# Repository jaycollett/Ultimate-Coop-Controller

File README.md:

# Ultimate-Coop-Controller
Arduino controlled chicken coop sensing and automation

More details on this project soon....

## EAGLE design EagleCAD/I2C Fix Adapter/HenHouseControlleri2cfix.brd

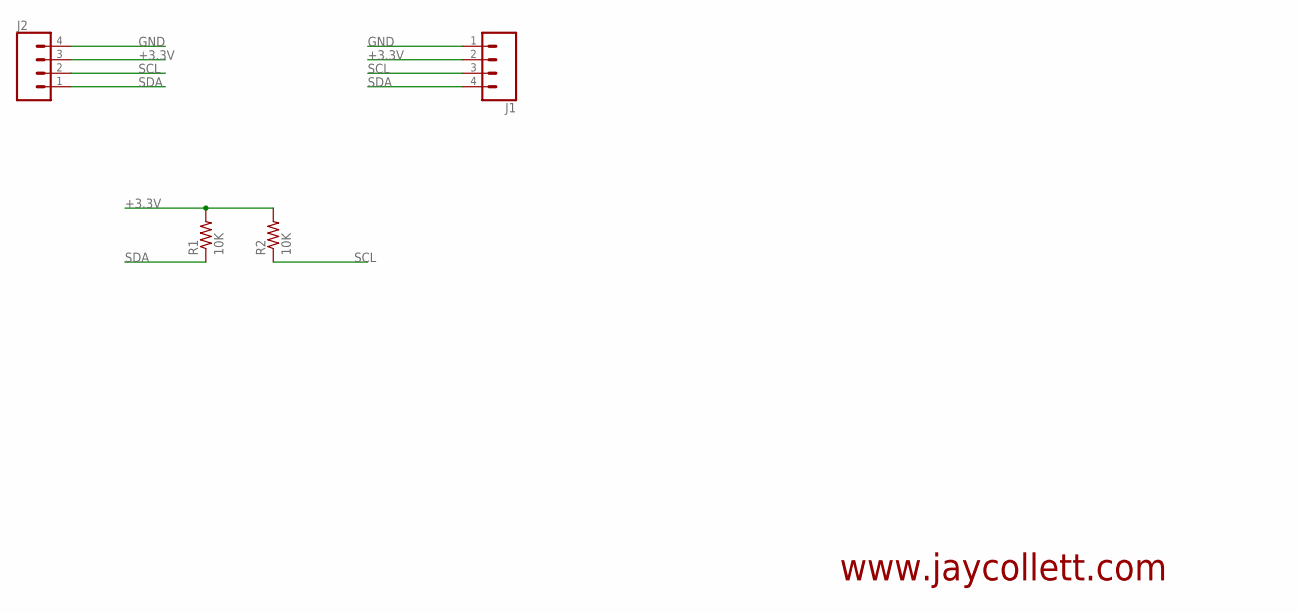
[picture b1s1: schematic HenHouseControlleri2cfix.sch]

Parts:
J1, J2: CONN_04LONGPADS; 1X04_LONGPADS
R1, R2: 10K; R0805

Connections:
+3.3V: J1.2, J2.3, R1.2, R2.2
GND: J1.1, J2.4
SCL: J1.3, J2.2, R2.1
SDA: J1.4, J2.1, R1.1

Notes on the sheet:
www.jaycollett.com

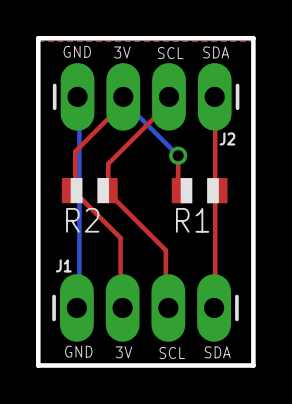
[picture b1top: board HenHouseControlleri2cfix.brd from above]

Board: 2 copper layers, 11.9 x 18.2 mm, 4 parts (0 on the bottom side), 4 nets.

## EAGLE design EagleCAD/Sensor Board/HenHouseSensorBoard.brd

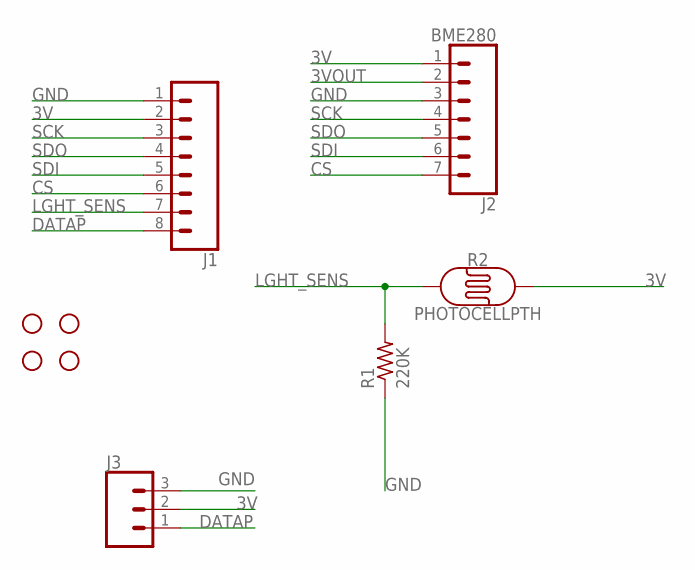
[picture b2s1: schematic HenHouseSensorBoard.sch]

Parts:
H1, H2, H3, H4: STAND-OFF
J1: CONN_08LONGPADS; 1X08_LONGPADS
J2: BME280; 1X07_LONGPADS
J3: CONN_03LONGPADS; 1X03_LONGPADS
R1: 220K; 0207/9
R2: PHOTOCELLPTH; PHOTOCELL

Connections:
3V: J1.2, J2.1, J3.2, R2.2
3VOUT: J2.2
CS: J1.6, J2.7
DATAP: J1.8, J3.1
GND: J1.1, J2.3, J3.3, R1.1
LGHT_SENS: J1.7, R1.2, R2.1
SCK: J1.3, J2.4
SDI: J1.5, J2.6
SDO: J1.4, J2.5

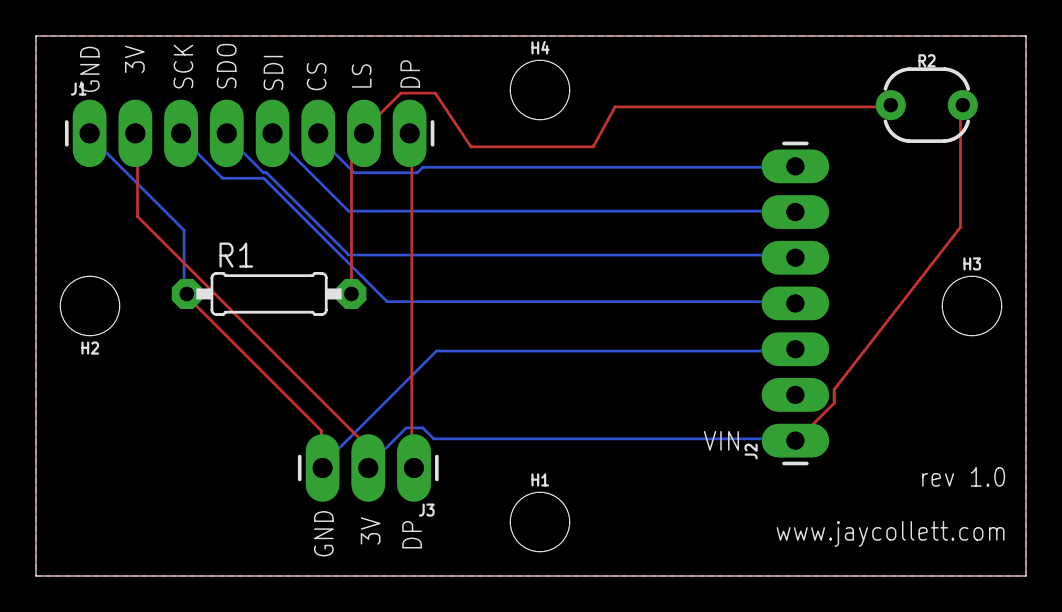
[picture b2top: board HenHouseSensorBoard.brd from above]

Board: 2 copper layers, 55.0 x 30.0 mm, 9 parts (0 on the bottom side), 8 nets.

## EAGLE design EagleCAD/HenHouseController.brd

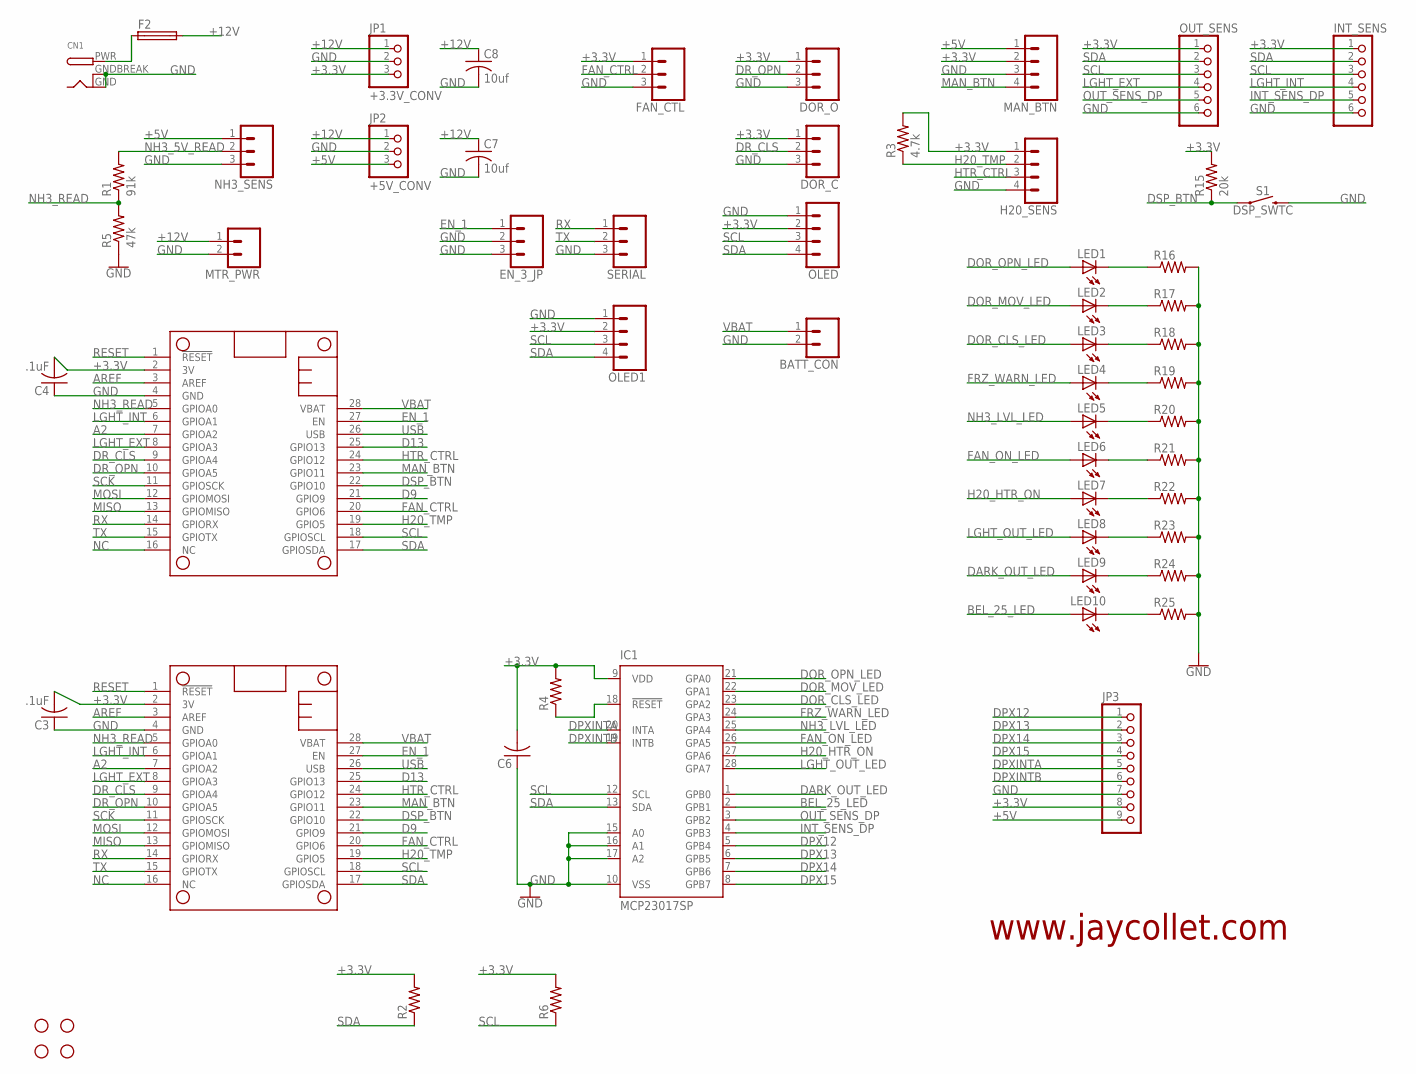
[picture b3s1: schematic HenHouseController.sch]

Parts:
BATT_CON: CONN_02; 1X02
C3, C4: .1uF; C0805
C6: C-USC0805; C0805
C7, C8: 10uf; C0805
CN1: DCBARRELPTH; DCJACK_2MM_PTH
DOR_C: CONN_03; 1X03
DOR_O: CONN_03; 1X03
EN_3_JP: CONN_03; 1X03
F2: SH25
FAN_CTL: CONN_03; 1X03
FEATHER_1, FEATHER_2: FEATHERWING_NODIM; FEATHERWING_DIM
H1, H2, H3, H4: STAND-OFF
H20_SENS: CONN_04; 1X04
IC1: MCP23017SP; DIL28-3
INT_SENS: PINHD-1X6; 1X06
JP1: +3.3V_CONV; 1X03
JP2: +5V_CONV; 1X03
JP3: PINHD-1X9; 1X09-BIG
LED1, LED2, LED3, LED4, LED5, LED6, LED7, LED8, LED9, LED10: LEDCHIPLED_0805; CHIPLED_0805
MAN_BTN: CONN_04; 1X04
MTR_PWR: CONN_02; 1X02
NH3_SENS: CONN_03; 1X03
OLED, OLED1: CONN_04; 1X04
OUT_SENS: PINHD-1X6; 1X06
R1: 91k; R0805
R2, R6: R-US_M0805; M0805
R3: 4.7k; R0805
R4, R16, R17, R18, R19, R20, R21, R22, R23, R24, R25: R-US_R0805; R0805
R5: 47k; R0805
R15: 20k; M0805
S1: DSP_SWTC; TACTILE_SWITCH_PTH_6.0MM
SERIAL: CONN_03; 1X03

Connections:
+3.3V: C3.2, C4.2, C6.2, DOR_C.1, DOR_O.1, FAN_CTL.1, FEATHER_1.2 (3V), FEATHER_2.2 (3V), H20_SENS.1, IC1.9 (VDD), INT_SENS.1, JP1.3, JP3.8, MAN_BTN.2, OLED.2, OLED1.2, OUT_SENS.1, R2.2, R3.2, R4.2, R6.2, R15.2
+5V: JP2.3, JP3.9, MAN_BTN.1, NH3_SENS.1
+12V: C7.1, C8.1, F2.2, JP1.1, JP2.1, MTR_PWR.1
A2: FEATHER_1.7 (GPIOA2), FEATHER_2.7 (GPIOA2)
AREF: FEATHER_1.3 (AREF), FEATHER_2.3 (AREF)
BEL_25_LED: IC1.2 (GPB1), LED10.A
D9: FEATHER_1.21 (GPIO9), FEATHER_2.21 (GPIO9)
D13: FEATHER_1.25 (GPIO13), FEATHER_2.25 (GPIO13)
DARK_OUT_LED: IC1.1 (GPB0), LED9.A
DOR_CLS_LED: IC1.23 (GPA2), LED3.A
DOR_MOV_LED: IC1.22 (GPA1), LED2.A
DOR_OPN_LED: IC1.21 (GPA0), LED1.A
DPX12: IC1.5 (GPB4), JP3.1
DPX13: IC1.6 (GPB5), JP3.2
DPX14: IC1.7 (GPB6), JP3.3
DPX15: IC1.8 (GPB7), JP3.4
DPXINTA: IC1.20 (INTA), JP3.5
DPXINTB: IC1.19 (INTB), JP3.6
DR_CLS: DOR_C.2, FEATHER_1.9 (GPIOA4), FEATHER_2.9 (GPIOA4)
DR_OPN: DOR_O.2, FEATHER_1.10 (GPIOA5), FEATHER_2.10 (GPIOA5)
DSP_BTN: FEATHER_1.22 (GPIO10), FEATHER_2.22 (GPIO10), R15.1, S1.1
EN_1: EN_3_JP.1, FEATHER_1.27 (EN), FEATHER_2.27 (EN)
FAN_CTRL: FAN_CTL.2, FEATHER_1.20 (GPIO6), FEATHER_2.20 (GPIO6)
FAN_ON_LED: IC1.26 (GPA5), LED6.A
FRZ_WARN_LED: IC1.24 (GPA3), LED4.A
GND: BATT_CON.2, C3.1, C4.1, C6.1, C7.2, C8.2, CN1.GND, CN1.GNDBREAK, DOR_C.3, DOR_O.3, EN_3_JP.2, EN_3_JP.3, FAN_CTL.3, FEATHER_1.4 (GND), FEATHER_2.4 (GND), H20_SENS.4, IC1.10 (VSS), IC1.15 (A0), IC1.16 (A1), IC1.17 (A2), INT_SENS.6, JP1.2, JP2.2, JP3.7, MAN_BTN.3, MTR_PWR.2, NH3_SENS.3, OLED.1, OLED1.1, OUT_SENS.6, R5.1, R16.2, R17.2, R18.2, R19.2, R20.2, R21.2, R22.2, R23.2, R24.2, R25.2, S1.3 (2), SERIAL.3
H20_HTR_ON: IC1.27 (GPA6), LED7.A
H20_TMP: FEATHER_1.19 (GPIO5), FEATHER_2.19 (GPIO5), H20_SENS.2, R3.1
HTR_CTRL: FEATHER_1.24 (GPIO12), FEATHER_2.24 (GPIO12), H20_SENS.3
INT_SENS_DP: IC1.4 (GPB3), INT_SENS.5
LGHT_EXT: FEATHER_1.8 (GPIOA3), FEATHER_2.8 (GPIOA3), OUT_SENS.4
LGHT_INT: FEATHER_1.6 (GPIOA1), FEATHER_2.6 (GPIOA1), INT_SENS.4
LGHT_OUT_LED: IC1.28 (GPA7), LED8.A
MAN_BTN: FEATHER_1.23 (GPIO11), FEATHER_2.23 (GPIO11), MAN_BTN.4
MISO: FEATHER_1.13 (GPIOMISO), FEATHER_2.13 (GPIOMISO)
MOSI: FEATHER_1.12 (GPIOMOSI), FEATHER_2.12 (GPIOMOSI)
unnamed: CN1.PWR, F2.1
unnamed: IC1.18 (!RESET), R4.1
unnamed: LED1.C, R16.1
unnamed: LED2.C, R17.1
unnamed: LED3.C, R18.1
unnamed: LED4.C, R19.1
unnamed: LED5.C, R20.1
unnamed: LED6.C, R21.1
unnamed: LED7.C, R22.1
unnamed: LED8.C, R23.1
unnamed: LED9.C, R24.1
unnamed: LED10.C, R25.1
NC: FEATHER_1.16 (NC), FEATHER_2.16 (NC)
NH3_5V_READ: NH3_SENS.2, R1.2
NH3_LVL_LED: IC1.25 (GPA4), LED5.A
NH3_READ: FEATHER_1.5 (GPIOA0), FEATHER_2.5 (GPIOA0), R1.1, R5.2
OUT_SENS_DP: IC1.3 (GPB2), OUT_SENS.5
RESET: FEATHER_1.1 (!RESET), FEATHER_2.1 (!RESET)
RX: FEATHER_1.14 (GPIORX), FEATHER_2.14 (GPIORX), SERIAL.1
SCK: FEATHER_1.11 (GPIOSCK), FEATHER_2.11 (GPIOSCK)
SCL: FEATHER_1.18 (GPIOSCL), FEATHER_2.18 (GPIOSCL), IC1.12 (SCL), INT_SENS.3, OLED.3, OLED1.3, OUT_SENS.3, R6.1
SDA: FEATHER_1.17 (GPIOSDA), FEATHER_2.17 (GPIOSDA), IC1.13 (SDA), INT_SENS.2, OLED.4, OLED1.4, OUT_SENS.2, R2.1
TX: FEATHER_1.15 (GPIOTX), FEATHER_2.15 (GPIOTX), SERIAL.2
USB: FEATHER_1.26 (USB), FEATHER_2.26 (USB)
VBAT: BATT_CON.1, FEATHER_1.28 (VBAT), FEATHER_2.28 (VBAT)

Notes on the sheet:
www.jaycollet.com

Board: 2 copper layers, 59 parts (0 on the bottom side), 61 nets, no tracks yet.

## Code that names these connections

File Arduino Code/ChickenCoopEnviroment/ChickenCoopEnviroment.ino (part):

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#define DOOR_OPENED_PIN A5
#define MANUAL_DOOR_CTRL 11
#define NH3_GAS_PIN A0
#define FAN_CTRL_PIN 6

// Define some other compiler time statics
#define SEALEVELPRESSURE_HPA (1013.25)
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#define DOOR_CLOSED_LED 2
#define FREEZE_WARN_LED 3
#define NH3_WARN_LED 4
#define FAN_ON_LED 5
#define H20_HEAT_LED 6
#define LIGHT_OUT_LED 7
#define DARK_OUT_LED 8
#define BELOW_25_LED 9

// Define our long and lat for use in calc of sunrise/sunset
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  pinExpander.pinMode(DOOR_CLOSED_LED, OUTPUT);
  pinExpander.pinMode(FREEZE_WARN_LED, OUTPUT);
  pinExpander.pinMode(NH3_WARN_LED, OUTPUT);
  pinExpander.pinMode(FAN_ON_LED, OUTPUT);
  pinExpander.pinMode(H20_HEAT_LED, OUTPUT);
  pinExpander.pinMode(LIGHT_OUT_LED, OUTPUT);
  pinExpander.pinMode(DARK_OUT_LED, OUTPUT);
  pinExpander.pinMode(BELOW_25_LED, OUTPUT);


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  currentMillis = millis();
  if (currentMillis - previousFanCheckMillis >= fanCheckInterval) {
    if (!fanOn && (Celcius2Fahrenheit(bmeInside.readTemperature()) > 80) && (Celcius2Fahrenheit(bmeInside.readTemperature()) < 90)) {
      digitalWrite(FAN_CTRL_PIN, HIGH);
      fanOn = true;
      pinExpander.digitalWrite(FAN_ON_LED, HIGH);
      mqttclient.publish("Coop/Inside/Fan", "On");
    } else if (fanOn && (Celcius2Fahrenheit(bmeInside.readTemperature()) > 80) && (Celcius2Fahrenheit(bmeInside.readTemperature()) < 90)) {
      // cycle fan off
      digitalWrite(FAN_CTRL_PIN, LOW);
      fanOn = false;
      pinExpander.digitalWrite(FAN_ON_LED, LOW);
      mqttclient.publish("Coop/Inside/Fan", "Off");
    } else if (fanOn && (Celcius2Fahrenheit(bmeInside.readTemperature()) < 80)) {
      // temp is low enough, turn fan off
      digitalWrite(FAN_CTRL_PIN, LOW);
      fanOn = false;
      pinExpander.digitalWrite(FAN_ON_LED, LOW);
      mqttclient.publish("Coop/Inside/Fan", "Off");
    } else if (!fanOn && (Celcius2Fahrenheit(bmeInside.readTemperature()) > 90)) {
      digitalWrite(FAN_CTRL_PIN, HIGH);
      fanOn = true;
      pinExpander.digitalWrite(FAN_ON_LED, HIGH);
      mqttclient.publish("Coop/Inside/Fan", "On");
    }
    previousFanCheckMillis = currentMillis; // update the time we last checked the fan status
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    if (doorOpen && isAfterSunSet()) {
      debugln("Door is open and it's after sun set...closing door.");
      pinExpander.digitalWrite(LIGHT_OUT_LED, LOW);
      pinExpander.digitalWrite(DARK_OUT_LED, HIGH);
      closeDoor();
    } else if (!doorOpen && isAfterSunRise() && (Celcius2Fahrenheit(bmeOutside.readTemperature()) > MIN_OUTSIDE_TEMP) && !isAfterSunSet()) {
      debugln("Door is NOT open and it's after sunrise above min outside temp and NOT after sun set.");
      pinExpander.digitalWrite(LIGHT_OUT_LED, HIGH);
      pinExpander.digitalWrite(DARK_OUT_LED, LOW);
      openDoor();
    } else if (!doorOpen && isAfterSunRise() && (Celcius2Fahrenheit(bmeOutside.readTemperature()) <= MIN_OUTSIDE_TEMP && !isAfterSunSet())) {
      debugln("Door is NOT open and it's after sunrise, NOT after sun set and TOO COLD to open door..");
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
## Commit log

2018-02-10 Tweaking system reset on hard faults and door errors
2018-02-12 adding coupous delays to see attempt to eliminate throttling...
2018-02-12 updating delays a bit
2018-02-12 adding a few io.run commands
2018-02-12 updating firmware version
2018-02-12 adding some tweaks to timing
2018-02-12 fixed some errors in comment spelling
2018-02-12 fixing up more comments
2018-02-15 adding travis config file
2018-02-15 updating .gitignore
2018-02-15 adding badges
2018-02-15 trying to fix up travis file
2018-02-15 trying new library names in travis file for arduino
2018-02-15 fixing space issues in travis file
2018-02-16 moving to mqtt broker instead of aio
2018-02-16 moving all code to mqtt, trying adafruit mqtt
2018-02-17 moving away from AIO to local mqtt broker
2018-02-17 clean build for new mqtt version
2018-02-17 verified mqtt build and function
2018-02-18 adding code to reset wifi,trying to fix hard freezes
2018-02-18 ethernet variant
2018-02-18 fixing bug with door functions
2018-02-18 Revert "fixing bug with door functions"
    This reverts commit b27e2dbd5129d6d3fe4b7bb65b53bb7c29472189.
2018-02-18 Revert "ethernet variant"
    This reverts commit 3d5cfc036778db048612a3afc66ad936b0c4d915.
2018-02-18 Revert "Revert "fixing bug with door functions""
    This reverts commit 64e1ad4989a43121b167b2fd365ea41dc7a1e755.
2018-02-18 fixing bug with door transition
2018-02-18 Modified from master to use ethernet library
2018-02-19 adding cstr conversion to mqtt msgs
2018-02-19 fixing up some delays with mqtt
2018-02-19 fixin up some mqtt errors
2018-02-19 adding more debug output
2018-02-20 trying code to fix publish of door status
2018-03-19 updating travis file for building
2018-03-20 trying to fixup travis file for builds
2018-03-20 updating badge url to go to travis-ci.org
2018-03-20 updating license url
2018-03-26 fixing the client id on mqtt conect that was using server ip

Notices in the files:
Arduino Code/ChickenCoopEnviroment/ChickenCoopEnviroment.ino:
This work (excluding external modules/libraries) is licensed under CC BY-SA 4.0
parts and their libraries:
SparkFun-Connectors: Licensing: Creative Commons ShareAlike 4.0 International - https://creativecommons.org/licenses/by-sa/4.0
